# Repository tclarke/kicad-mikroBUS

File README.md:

# kicad-mikroBUS
Kicad files for creating MikroBUS host boards and modules.

## Installation
Copy the templates to your user templates directory.
Add the schematic library and footprint module in the symbol and footprint library managers.

### Templates
There are three templates for the three module sizes specified in the MikroBUS standard. Each contains a MikroBUS module schematic symbol with some buses pulled out for the SPI, I2C, and UART. There are corresponding footprints in the PCB layouts along with the appropriately sized board edge cuts.

### Schematic symbols
There are symbols for the MikroBUS pins for use on host boards and modules. The only difference is the swapping of the UART RX and TX labels per the spec.

### Footprints
There are footprints for host boards and modules. They follow the appropriate standards and guidance in the MikroBUS standards spec.

## Contributing
Feel free to contribute, pull requests and patches are welcome.

## Examples
### Host Board
I've included an example host board which is a STM32 Black Pill (or Blue Pill) adapter with 4 MikroBUS ports. Since the board doesn't have enough serial buses for all of the ports, there is some sharing. Below are the mappings.

| MikroBUS Bus   | Port 1 | Port 2 | Port 3 | Port 4 |
|----------------|--------|--------|--------|--------|
| Analog         | A1     | A2     | A3     | A4     |
| Reset          | RST    | RST    | RST    | RST    |
| SPI            | SPI1   | SPI1   | SPI2   | SPI2   |
| I<sup>2</sup>C | I2C1   | I2C2   | I2C1   | I2C2   |
| UART           | UART1  | UART2  | UART2  | UART1  |
| Interrupt      | INT1   | INT2   | INT3   | INT4   |
| PWM            | PWM1   | A3     | A4     | A2     |

This mixes up the sharing a bit to minimize impact for boards requiring multiple, similar buses. Mappings to the STM32 chip are as follows.

| Function       | STM32 Pin |
|----------------|-----------|
| RST            | NRST      |
| A1             | PA0       |
| A2             | PA1       |
| A3             | PB0       |
| A4             | PB1       |
| INT1           | PB3       |
| INT2           | PB4       |
| INT3           | PB5       |
| INT4           | PB8       |
| PWM1           | PA8       |
| CS1   (SPI)    | PA4       |
| SCK1  (SPI)    | PA5       |
| MISO1 (SPI)    | PA6       |
| MOSI1 (SPI)    | PA7       |
| CS2   (SPI)    | PB12      |
| SCK2  (SPI)    | PB13      |
| MISO2 (SPI)    | PB14      |
| MOSI2 (SPI)    | PB15      |
| SDA1 (I<sup>2</sup>C) | PB7  |
| SCL1 (I<sup>2</sup>C) | PB6  |
| SDA2 (I<sup>2</sup>C) | PB11 |
| SCL2 (I<sup>2</sup>C) | PB10 |
| TX1 (UART)     | PA9       |
| RX1 (UART)     | PA10      |
| TX2 (UART)     | PA2       |
| RX2 (UART)     | PA3       |

### Module
There is also an example module board on a small (Mini) board layout. It's a simple Si5351 programmable clock interface with SMA adapters. This is an I<sup>2</sup>C driven board.

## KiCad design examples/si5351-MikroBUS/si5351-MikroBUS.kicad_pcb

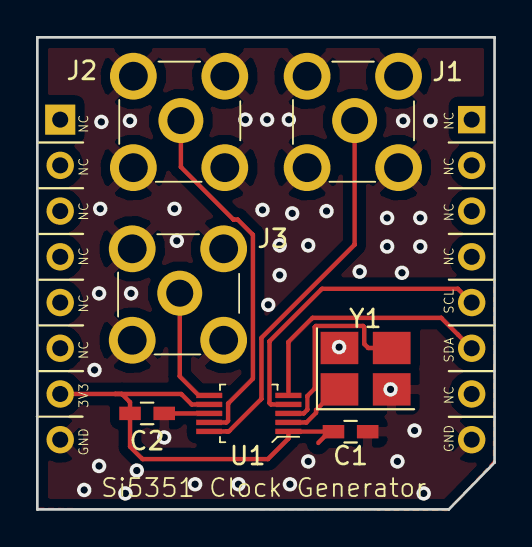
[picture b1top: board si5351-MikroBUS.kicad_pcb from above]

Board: 2 copper layers, 25.4 x 26.2 mm, 9 parts (1 on the bottom side), 9 nets.

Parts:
*: MIKROCLICK_LOGO; MIKROBUS_LOGO
C1, C2: 0.1u; C_0603_HandSoldering
CON101: MIKROBUS_MODULE_CONN
J1, J2, J3: 5-1814832-1; RF_SMA_Vertical_5-1814832-1
U1: SI5351A-B-GT; MSOP-10_W3mm
Y1: 27 MHz; Crystal_SMD_3225-4pin_3.2x2.5mm_HandSoldering

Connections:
+3V3: C1.1, C2.2, CON101.P7, U1.1, U1.7
/SCL: CON101.P12, U1.4
/SDA: CON101.P11, U1.5
GND: C1.2, C2.1, CON101.P8, CON101.P9, J1.1, J2.1, J3.1, U1.8, Y1.2, Y1.4
unnamed: J1.2, U1.10
unnamed: J2.2, U1.9
unnamed: J3.2, U1.6
unnamed: U1.2, Y1.1
unnamed: U1.3, Y1.3

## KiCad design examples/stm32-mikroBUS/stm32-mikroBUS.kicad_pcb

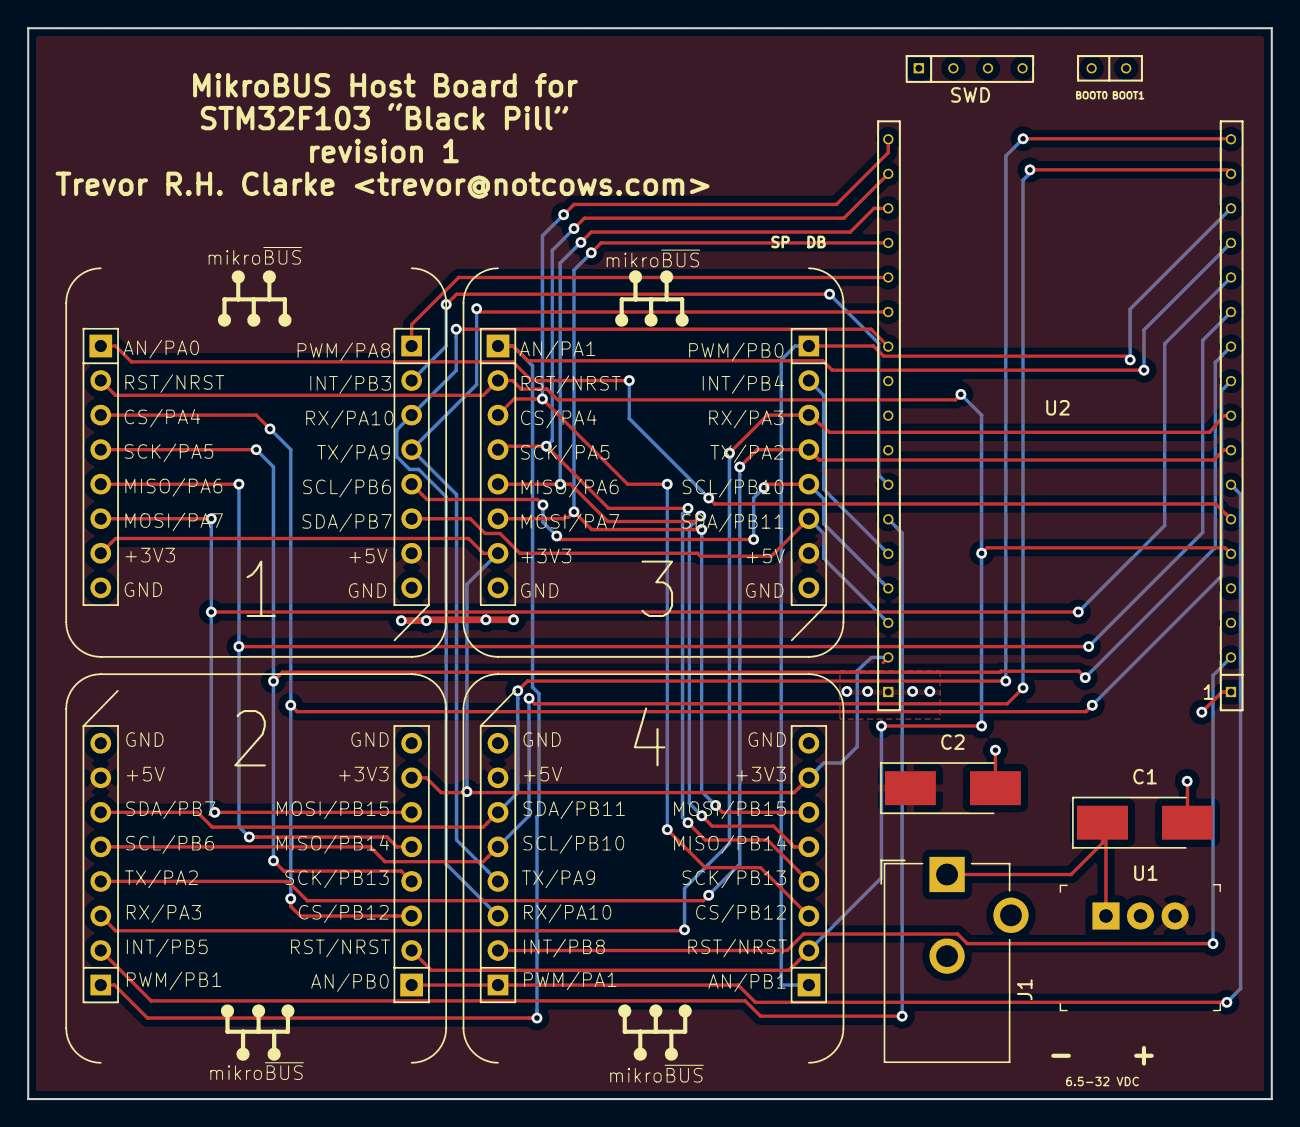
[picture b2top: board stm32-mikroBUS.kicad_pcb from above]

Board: 2 copper layers, 91.4 x 78.7 mm, 9 parts (0 on the bottom side), 30 nets.

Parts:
C1: 10u/50V; CP_Tantalum_Case-C_EIA-6032-28_Hand
C2: 22u/16V; CP_Tantalum_Case-C_EIA-6032-28_Hand
CON1: 1; MIKROBUS_HOST_CONN
CON2: 2; MIKROBUS_HOST_CONN
CON3: 3; MIKROBUS_HOST_CONN
CON4: 4; MIKROBUS_HOST_CONN
J1: 6.5-32 VDC; Barrel_Jack_CUI_PJ-102AH
U1: V7805-1000; 3-SIP_Module_V7805-1000
U2: BlackPill

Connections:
+3V3: CON1.P7, CON2.P7, CON3.P7, CON4.P7, U2.33
+5V: C2.1, CON1.P10, CON2.P10, CON3.P10, CON4.P10, U1.3
/A1: CON1.P1, U2.6
/A2: CON2.P1, CON4.P16, U2.7
/A3: CON2.P16, CON3.P1, U2.14
/A4: CON3.P16, CON4.P1, U2.15
/I1: CON1.P15, U2.28
/I2: CON2.P15, U2.29
/I3: CON3.P15, U2.30
/I4: CON4.P15, U2.2
/MISO1: CON1.P5, CON2.P5, U2.12
/MISO2: CON3.P5, CON4.P5, U2.20
/MOSI1: CON1.P6, CON2.P6, U2.13
/MOSI2: CON3.P6, CON4.P6, U2.21
/PWM1: CON1.P16, U2.22
/RX1: CON1.P14, CON4.P14, U2.24
/RX2: CON2.P14, CON3.P14, U2.9
/SCK1: CON1.P4, CON2.P4, U2.11
/SCK2: CON3.P4, CON4.P4, U2.19
/SCL1: CON1.P12, CON3.P12, U2.31
/SCL2: CON2.P12, CON4.P12, U2.16
/SDA1: CON1.P11, CON3.P11, U2.32
/SDA2: CON2.P11, CON4.P11, U2.17
/SS1: CON1.P3, CON2.P3, U2.10
/SS2: CON3.P3, CON4.P3, U2.18
/TX1: CON1.P13, CON4.P13, U2.23
/TX2: CON2.P13, CON3.P13, U2.8
GND: C1.2, C2.2, CON1.P8, CON1.P9, CON2.P8, CON2.P9, CON3.P8, CON3.P9, CON4.P8, CON4.P9, J1.2, U1.2, U2.1, U2.34
unnamed: C1.1, J1.1, U1.1
unnamed: CON1.P2, CON2.P2, CON3.P2, CON4.P2, U2.5

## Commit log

2019-02-13 Added examples
